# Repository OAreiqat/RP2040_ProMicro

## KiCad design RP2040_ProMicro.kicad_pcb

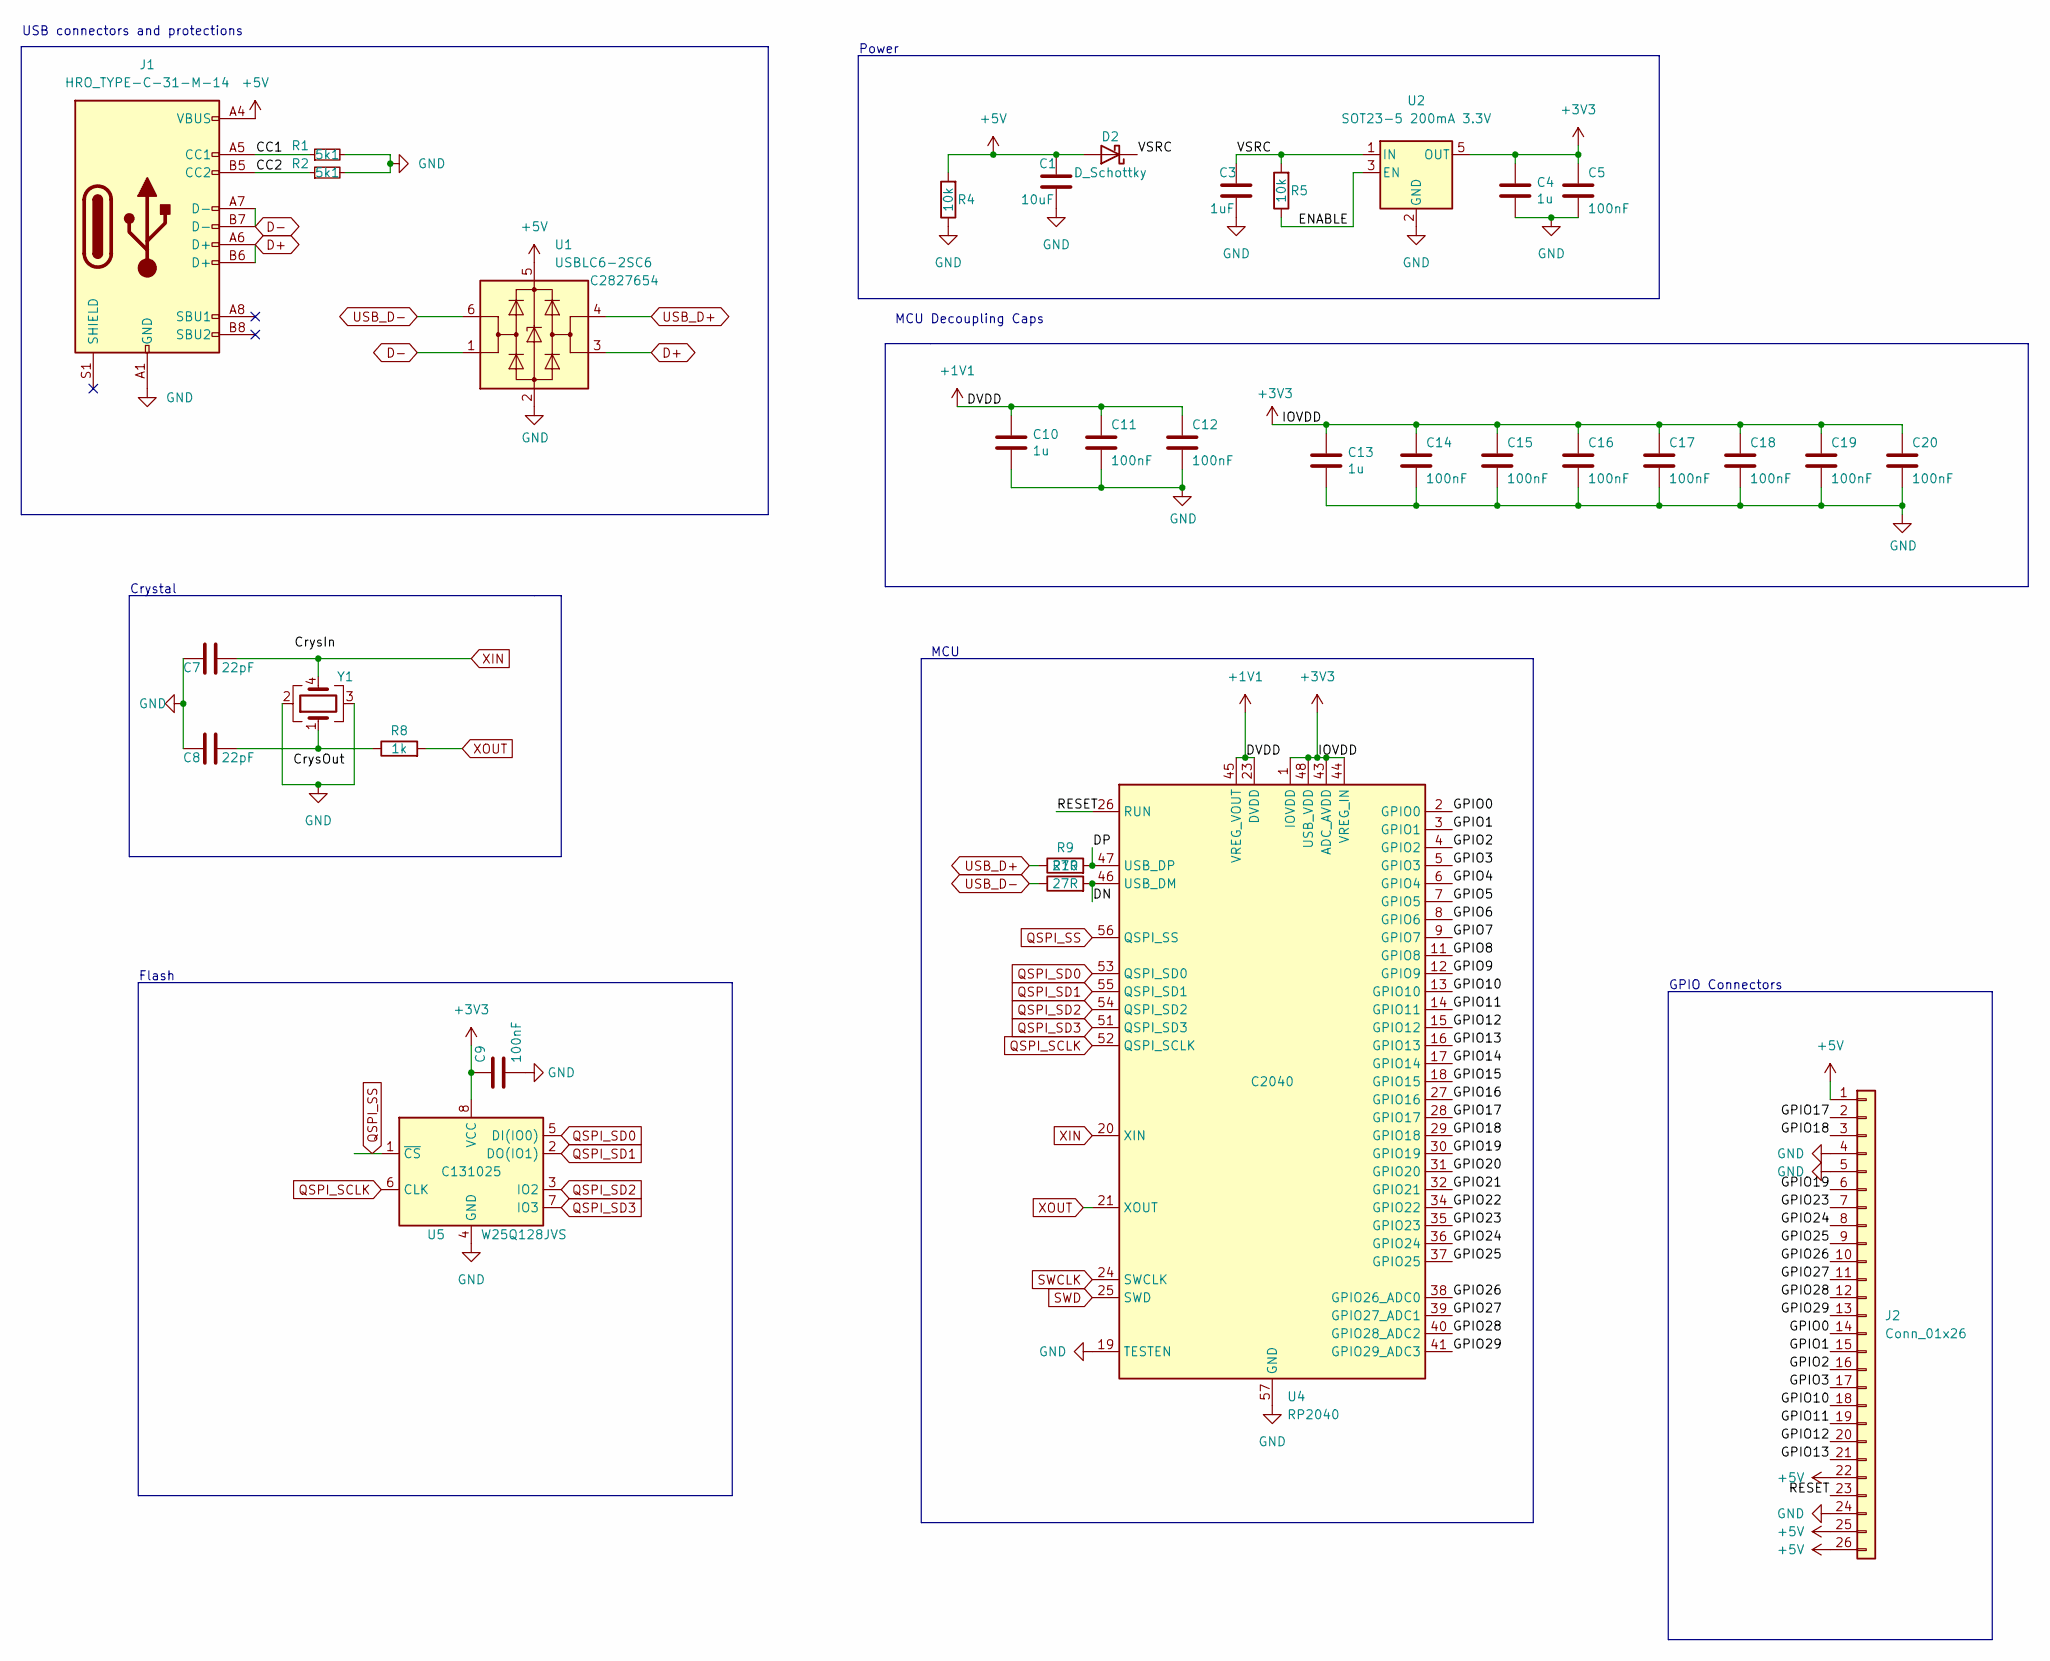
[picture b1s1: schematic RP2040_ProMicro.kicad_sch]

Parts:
C1: 10uF; C_0402_1005Metric; LCSC C15525
C3: 1uF; C_0402_1005Metric; LCSC C14445
C4, C10, C13: 1u; C_0402_1005Metric; LCSC C14445
C5, C9, C11, C12, C14, C15, C16, C17, C18, C19, C20: 100nF; C_0402_1005Metric; LCSC C1525
C7, C8: 22pF; C_0402_1005Metric; LCSC C70464
D2: D_Schottky; D_SOD-323; LCSC C22624
J1: HRO_TYPE-C-31-M-14; USB_C_Receptacle_HRO_TYPE-C-31-M-12; LCSC C165948
J2: Conn_01x26; promicrorp2040
R1, R2: 5k1; R_0402_1005Metric; LCSC C25905
R4, R5: 10k; R_0402_1005Metric; LCSC C60490
R8: 1k; R_0402_1005Metric; LCSC C106235
R9, R10: 27R; R_0402_1005Metric; LCSC C3017455
U1: USBLC6-2SC6; SOT-23-6; LCSC C2827654
U2: SOT23-5 200mA 3.3V; SOT-23-5; LCSC C11337
U4: RP2040; QFN-56-1EP_7x7mm_P0.4mm_EP3.2x3.2mm; LCSC C2040
U5: W25Q128JVS; SOIC-8_5.23x5.23mm_P1.27mm; LCSC C131025
Y1: Crystal_GND23; Crystal_SMD_3225-4Pin_3.2x2.5mm; LCSC C9002

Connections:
+1V1: C10.1, C11.2, C12.2, U4.23 (DVDD), U4.45 (VREG_VOUT), U4.50 (DVDD)
+3V3: C4.1, C5.2, C9.2, C13.1, C14.2, C15.2, C16.2, C17.2, C18.2, C19.2, C20.2, U2.5 (OUT), U4.1 (IOVDD), U4.10 (IOVDD), U4.22 (IOVDD), U4.33 (IOVDD), U4.42 (IOVDD), U4.43 (ADC_AVDD), U4.44 (VREG_IN), U4.48 (USB_VDD), U4.49 (IOVDD), U5.8 (VCC)
+5V: C1.1, D2.2 (A), J1.A4 (VBUS), J1.A9 (VBUS), J1.B4 (VBUS), J1.B9 (VBUS), J2.1, J2.22, J2.25, J2.26, R4.2, U1.5 (VBUS)
/CC1: J1.A5 (CC1), R1.1
/CC2: J1.B5 (CC2), R2.1
/DN: R10.2, U4.46 (USB_DM)
/DP: R9.2, U4.47 (USB_DP)
/ENABLE: R5.1, U2.3 (EN)
/GPIO0: J2.14, U4.2 (GPIO0)
/GPIO1: J2.15, U4.3 (GPIO1)
/GPIO2: J2.16, U4.4 (GPIO2)
/GPIO3: J2.17, U4.5 (GPIO3)
/GPIO4: U4.6 (GPIO4)
/GPIO5: U4.7 (GPIO5)
/GPIO6: U4.8 (GPIO6)
/GPIO7: U4.9 (GPIO7)
/GPIO8: U4.11 (GPIO8)
/GPIO9: U4.12 (GPIO9)
/GPIO10: J2.18, U4.13 (GPIO10)
/GPIO11: J2.19, U4.14 (GPIO11)
/GPIO12: J2.20, U4.15 (GPIO12)
/GPIO13: J2.21, U4.16 (GPIO13)
/GPIO14: U4.17 (GPIO14)
/GPIO15: U4.18 (GPIO15)
/GPIO16: U4.27 (GPIO16)
/GPIO17: J2.2, U4.28 (GPIO17)
/GPIO18: J2.3, U4.29 (GPIO18)
/GPIO19: J2.6, U4.30 (GPIO19)
/GPIO20: U4.31 (GPIO20)
/GPIO21: U4.32 (GPIO21)
/GPIO22: U4.34 (GPIO22)
/GPIO23: J2.7, U4.35 (GPIO23)
/GPIO24: J2.8, U4.36 (GPIO24)
/GPIO25: J2.9, U4.37 (GPIO25)
/GPIO26: J2.10, U4.38 (GPIO26_ADC0)
/GPIO27: J2.11, U4.39 (GPIO27_ADC1)
/GPIO28: J2.12, U4.40 (GPIO28_ADC2)
/GPIO29: J2.13, U4.41 (GPIO29_ADC3)
/RESET: J2.23, U4.26 (RUN)
/VSRC: C3.1, D2.1 (K), R5.2, U2.1 (IN)
D+: J1.A6 (D+), J1.B6 (D+), U1.3 (I/O2)
D-: J1.A7 (D-), J1.B7 (D-), U1.1 (I/O1)
GND: C1.2, C3.2, C4.2, C5.1, C7.2, C8.2, C9.1, C10.2, C11.1, C12.1, C13.2, C14.1, C15.1, C16.1, C17.1, C18.1, C19.1, C20.1, J1.A1 (GND), J1.A12 (GND), J1.B1 (GND), J1.B12 (GND), J2.4, J2.5, J2.24, R1.2, R2.2, R4.1, U1.2 (GND), U2.2 (GND), U4.19 (TESTEN), U4.57 (GND), U5.4 (GND), Y1.2, Y1.3
unnamed: C8.1, R8.1, Y1.1
QSPI_SCLK: U4.52 (QSPI_SCLK), U5.6 (CLK)
QSPI_SD0: U4.53 (QSPI_SD0), U5.5 (DI(IO0))
QSPI_SD1: U4.55 (QSPI_SD1), U5.2 (DO(IO1))
QSPI_SD2: U4.54 (QSPI_SD2), U5.3 (IO2)
QSPI_SD3: U4.51 (QSPI_SD3), U5.7 (IO3)
QSPI_SS: U4.56 (QSPI_SS), U5.1 (~CS)
SWCLK: U4.24 (SWCLK)
SWD: U4.25 (SWD)
USB_D+: R9.1, U1.4 (I/O2)
USB_D-: R10.1, U1.6 (I/O1)
XIN: C7.1, U4.20 (XIN), Y1.4
XOUT: R8.2, U4.21 (XOUT)

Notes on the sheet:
USB connectors and protections
Crystal
MCU
MCU Decoupling Caps
Flash
Power
GPIO Connectors

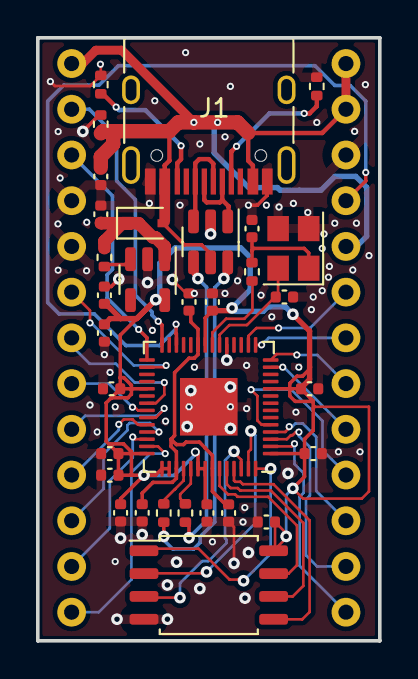
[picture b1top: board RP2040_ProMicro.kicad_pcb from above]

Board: 2 copper layers, 19.0 x 33.5 mm, 33 parts (0 on the bottom side), 42 nets.

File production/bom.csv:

Designator,Footprint,Quantity,Value,LCSC Part #
C1,C_0402_1005Metric,1,10uF,C15525
"C10, C13, C4",C_0402_1005Metric,3,1u,C14445
"C11, C12, C14, C15, C16, C17, C18, C19, C20, C5, C9",C_0402_1005Metric,11,100nF,C1525
C3,C_0402_1005Metric,1,1uF,C14445
"C7, C8",C_0402_1005Metric,2,22pF,C70464
D2,D_SOD-323,1,D_Schottky,C22624
J1,USB_C_Receptacle_HRO_TYPE-C-31-M-12,1,HRO_TYPE-C-31-M-14,C165948
J2,promicrorp2040,1,Conn_01x26,
"R1, R2",R_0402_1005Metric,2,5k1,C25905
"R10, R9",R_0402_1005Metric,2,27R,C3017455
"R4, R5",R_0402_1005Metric,2,10k,C60490
R8,R_0402_1005Metric,1,1k,C106235
U1,SOT-23-6,1,USBLC6-2SC6,C2827654
U2,SOT-23-5,1,SOT23-5 200mA 3.3V,C11337
U4,QFN-56-1EP_7x7mm_P0.4mm_EP3.2x3.2mm,1,RP2040,C2040
U5,SOIC-8_5.23x5.23mm_P1.27mm,1,W25Q128JVS,C131025
Y1,Crystal_SMD_3225-4Pin_3.2x2.5mm,1,Crystal_GND23,C9002

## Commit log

2023-01-05 Routing in progress
2023-01-06 added more vias around crystal
